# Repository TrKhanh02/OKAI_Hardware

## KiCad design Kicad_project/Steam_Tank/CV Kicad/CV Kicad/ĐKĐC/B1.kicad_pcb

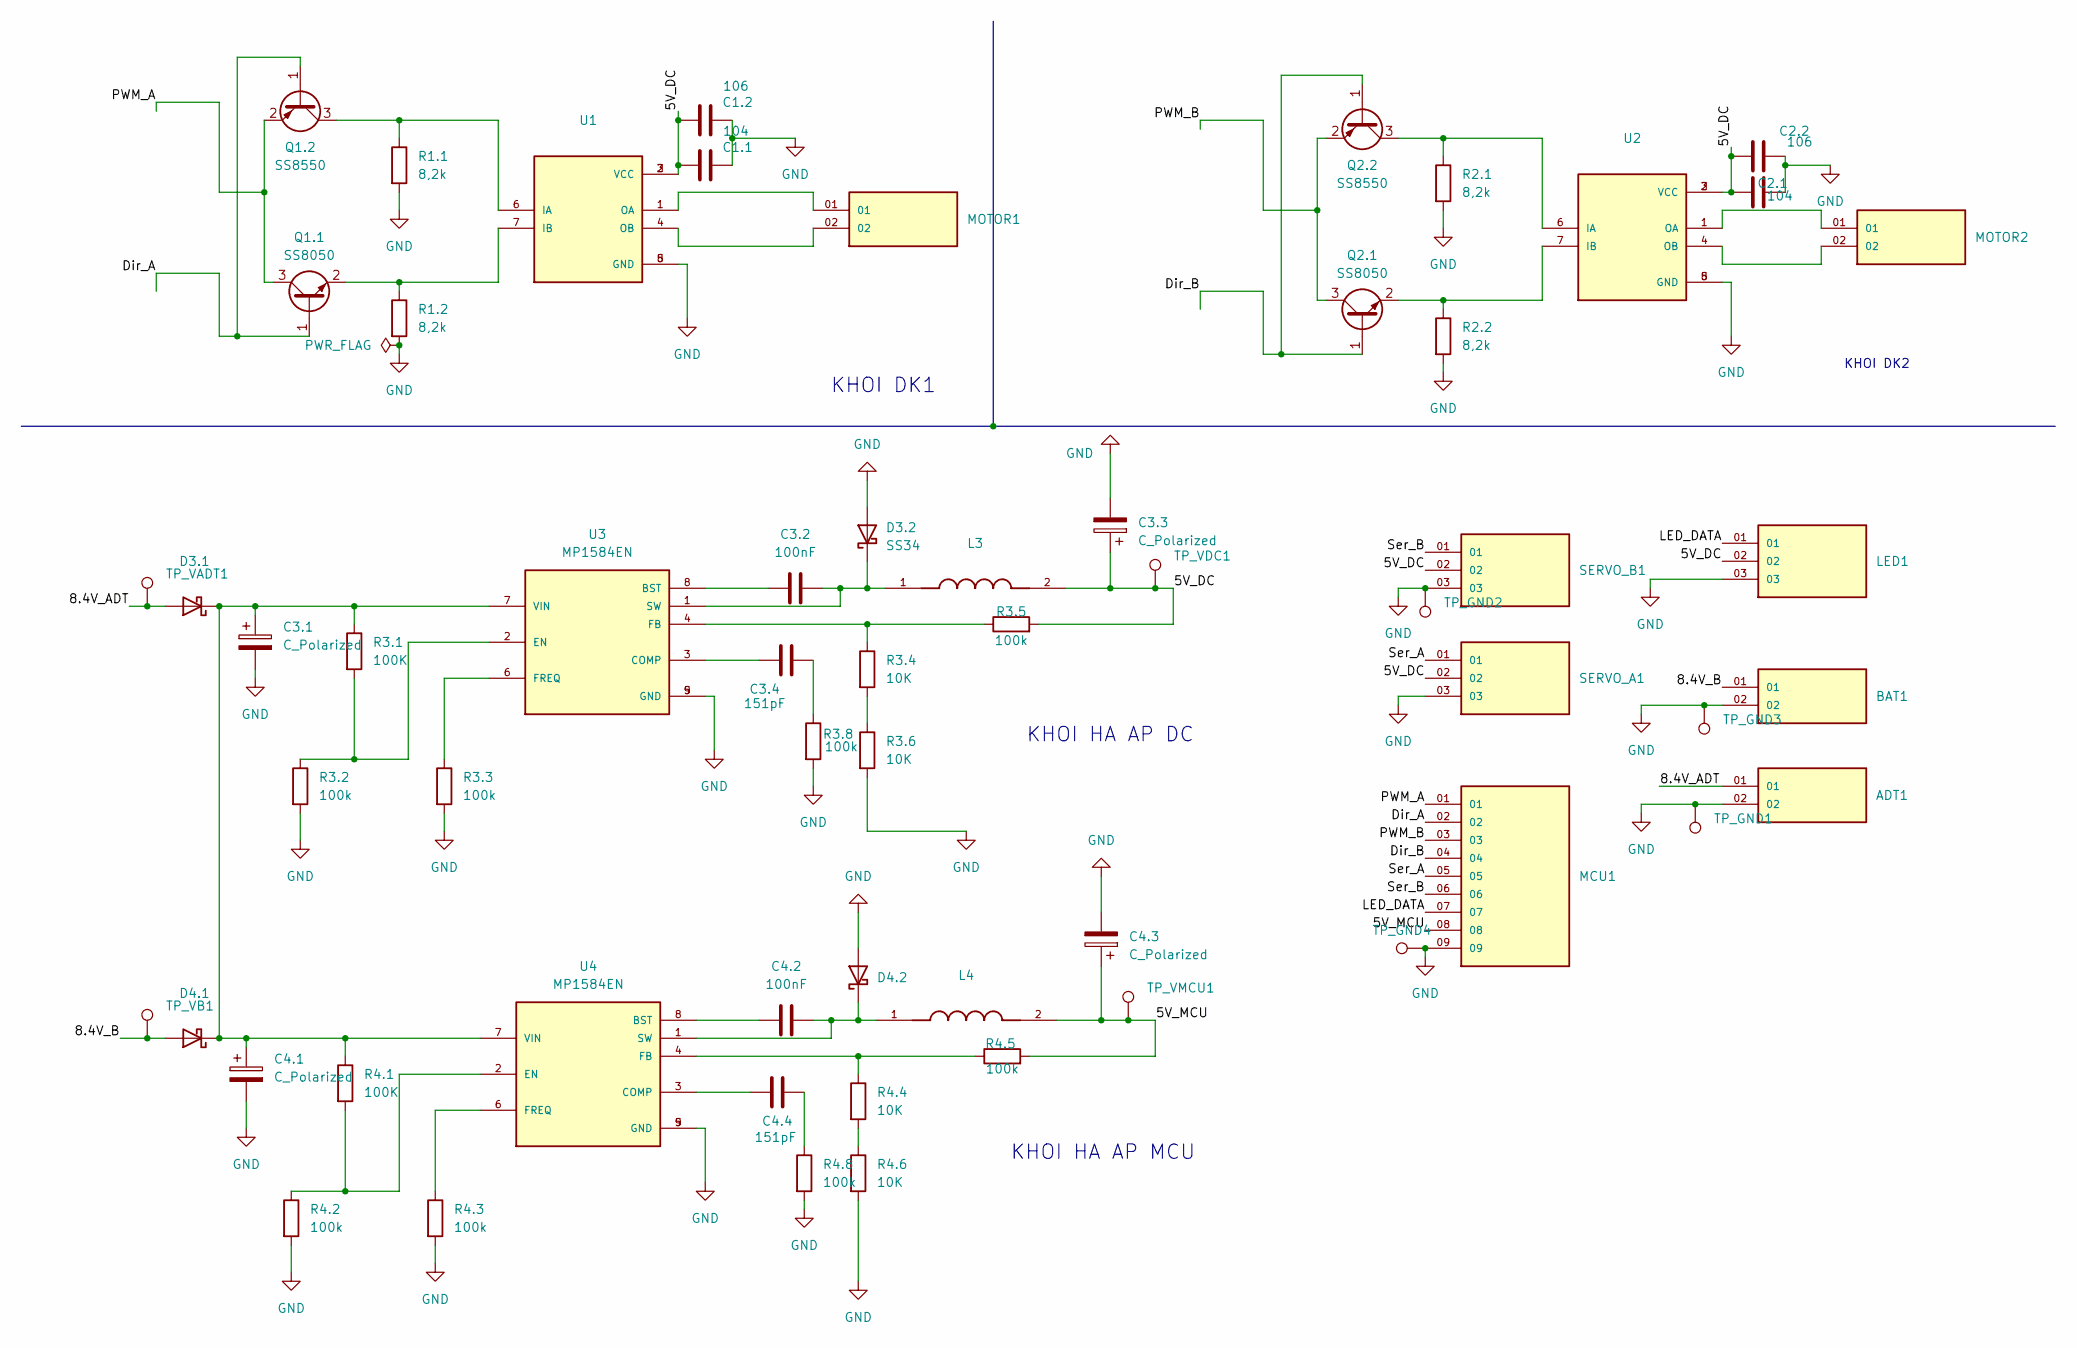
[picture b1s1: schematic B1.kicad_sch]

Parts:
ADT1: TSW-102-23-T-S; SAMTEC_TSW-102-23-T-S; PARTREV R
BAT1: TSW-102-23-T-S; SAMTEC_TSW-102-23-T-S; PARTREV R
C1.1, C2.1: 104; C_0805_2012Metric_Pad1.18x1.45mm_HandSolder
C1.2, C2.2: 106; C_0805_2012Metric_Pad1.18x1.45mm_HandSolder
C3.1, C3.3, C4.1, C4.3: C_Polarized; CP_Elec_6.3x7.7
C3.2, C4.2: 100nF; C_0805_2012Metric_Pad1.18x1.45mm_HandSolder
C3.4, C4.4: 151pF; C_0805_2012Metric_Pad1.18x1.45mm_HandSolder
D3.1, D3.2, D4.1, D4.2: SS34; D_SMA
L3, L4: SLF7032T-331MR22-2PF; IND_SLF7032T-331MR22-2PF; PARTREV N/A
LED1: MTSW-103-10-S-S-580; SAMTEC_MTSW-103-10-S-S-580; PARTREV R
MCU1: MTSW-109-12-L-S-805; SAMTEC_MTSW-109-12-L-S-805; PARTREV R
MOTOR1, MOTOR2: TSW-102-23-T-S; SAMTEC_TSW-102-23-T-S; PARTREV R
Q1.1, Q2.1: SS8050; SOT-23
Q1.2, Q2.2: SS8550; SOT-23
R1.1, R1.2, R2.1, R2.2: 8,2k; R_0805_2012Metric_Pad1.20x1.40mm_HandSolder
R3.1, R4.1: 100K; R_0805_2012Metric_Pad1.20x1.40mm_HandSolder
R3.2, R3.3, R3.5, R3.8, R4.2, R4.3, R4.5, R4.8: 100k; R_0805_2012Metric_Pad1.20x1.40mm_HandSolder
R3.4, R3.6, R4.4, R4.6: 10K; R_0805_2012Metric_Pad1.20x1.40mm_HandSolder
SERVO_A1: MTSW-103-10-S-S-580; SAMTEC_MTSW-103-10-S-S-580; PARTREV R
SERVO_B1: MTSW-103-10-S-S-580; SAMTEC_MTSW-103-10-S-S-580; PARTREV R
TP_GND1, TP_GND2, TP_GND3, TP_GND4: TestPoint; TestPoint_Pad_D1.0mm
TP_VADT1: TestPoint; TestPoint_Pad_D1.0mm
TP_VB1: TestPoint; TestPoint_Pad_D1.0mm
TP_VDC1: TestPoint; TestPoint_Pad_D1.0mm
TP_VMCU1: TestPoint; TestPoint_Pad_D1.0mm
U1, U2: L9110S; SOIC127P599X172-8N; PARTREV NA
U3, U4: MP1584EN; SOIC127P600X170-9N

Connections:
/5V_DC: C1.1.2, C1.2.2, C2.1.2, C2.2.1, C3.3.1, L3.2, LED1.02, R3.5.2, SERVO_A1.02, SERVO_B1.02, TP_VDC1.1, U1.2 (VCC), U1.3 (VCC), U2.2 (VCC), U2.3 (VCC)
/5V_MCU: C4.3.1, L4.2, MCU1.08, R4.5.2, TP_VMCU1.1
/8.4V_ADT: ADT1.01, D3.1.2 (A), TP_VADT1.1
/8.4V_B: BAT1.01, D4.1.2 (A), TP_VB1.1
/Dir_A: MCU1.02, Q1.1.1 (B), Q1.2.1 (B)
/Dir_B: MCU1.04, Q2.1.1 (B), Q2.2.1 (B)
/LED_DATA: LED1.01, MCU1.07
/PWM_A: MCU1.01, Q1.1.3 (C), Q1.2.2 (E)
/PWM_B: MCU1.03, Q2.1.3 (C), Q2.2.2 (E)
/Ser_A: MCU1.05, SERVO_A1.01
/Ser_B: MCU1.06, SERVO_B1.01
GND: ADT1.02, BAT1.02, C1.1.1, C1.2.1, C2.1.1, C2.2.2, C3.1.2, C3.3.2, C4.1.2, C4.3.2, D3.2.2 (A), D4.2.2 (A), LED1.03, MCU1.09, R1.1.2, R1.2.2, R2.1.2, R2.2.2, R3.2.2, R3.3.2, R3.6.2, R3.8.2, R4.2.2, R4.3.2, R4.6.2, R4.8.2, SERVO_A1.03, SERVO_B1.03, TP_GND1.1, TP_GND2.1, TP_GND3.1, TP_GND4.1, U1.5 (GND), U1.8 (GND), U2.5 (GND), U2.8 (GND), U3.5 (GND), U3.9 (GND), U4.5 (GND), U4.9 (GND)
unnamed: C3.4.1, R3.8.1
unnamed: C4.4.2, R4.8.1
unnamed: C3.1.1, C4.1.1, D3.1.1 (K), D4.1.1 (K), R3.1.1, R4.1.1, U3.7 (VIN), U4.7 (VIN)
unnamed: C3.2.2, D3.2.1 (K), L3.1, U3.1 (SW)
unnamed: C4.2.2, D4.2.1 (K), L4.1, U4.1 (SW)
unnamed: Q1.1.2 (E), R1.2.1, U1.7 (IB)
unnamed: Q1.2.3 (C), R1.1.1, U1.6 (IA)
unnamed: Q2.1.2 (E), R2.2.1, U2.7 (IB)
unnamed: Q2.2.3 (C), R2.1.1, U2.6 (IA)
unnamed: R3.4.2, R3.6.1
unnamed: R4.4.2, R4.6.1
unnamed: MOTOR1.01, U1.1 (OA)
unnamed: MOTOR1.02, U1.4 (OB)
unnamed: MOTOR2.01, U2.1 (OA)
unnamed: MOTOR2.02, U2.4 (OB)
unnamed: C3.2.1, U3.8 (BST)
unnamed: C3.4.2, U3.3 (COMP)
unnamed: R3.1.2, R3.2.1, U3.2 (EN)
unnamed: R3.4.1, R3.5.1, U3.4 (FB)
unnamed: R3.3.1, U3.6 (FREQ)
unnamed: C4.2.1, U4.8 (BST)
unnamed: C4.4.1, U4.3 (COMP)
unnamed: R4.1.2, R4.2.1, U4.2 (EN)
unnamed: R4.4.1, R4.5.1, U4.4 (FB)
unnamed: R4.3.1, U4.6 (FREQ)

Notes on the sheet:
KHOI HA AP DC
KHOI DK1
KHOI DK2
KHOI HA AP MCU

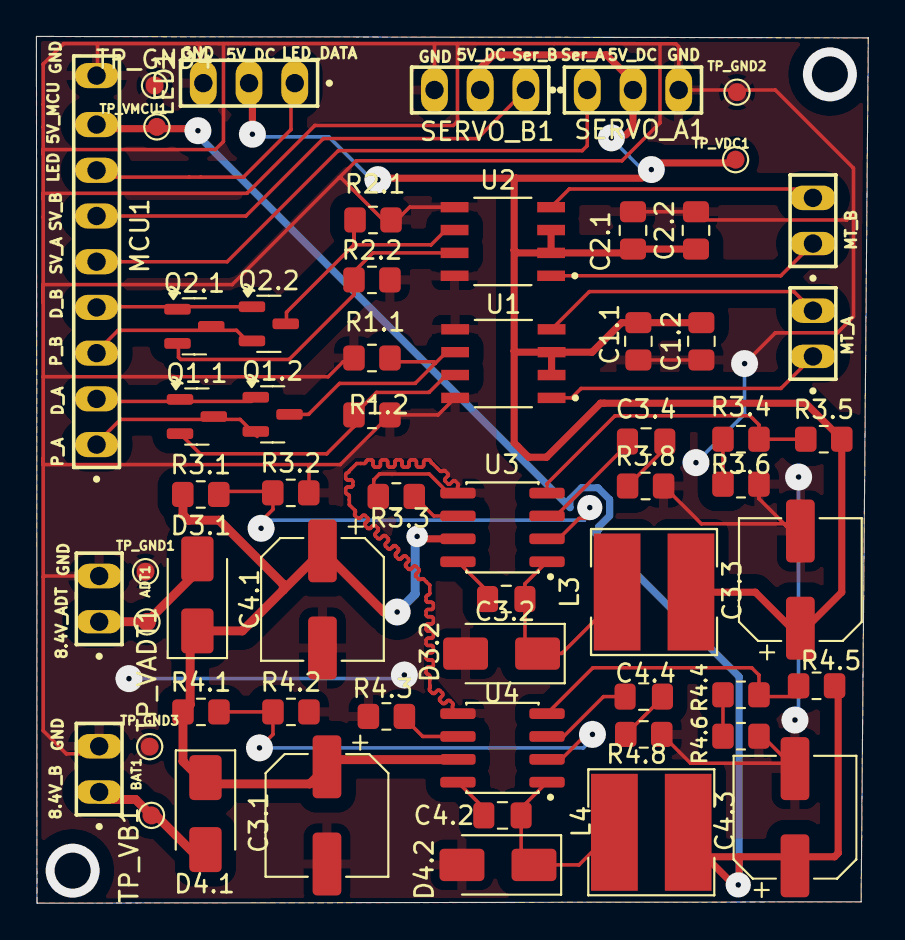
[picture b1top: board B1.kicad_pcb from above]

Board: 2 copper layers, 46.2 x 48.1 mm, 60 parts (0 on the bottom side), 37 nets.

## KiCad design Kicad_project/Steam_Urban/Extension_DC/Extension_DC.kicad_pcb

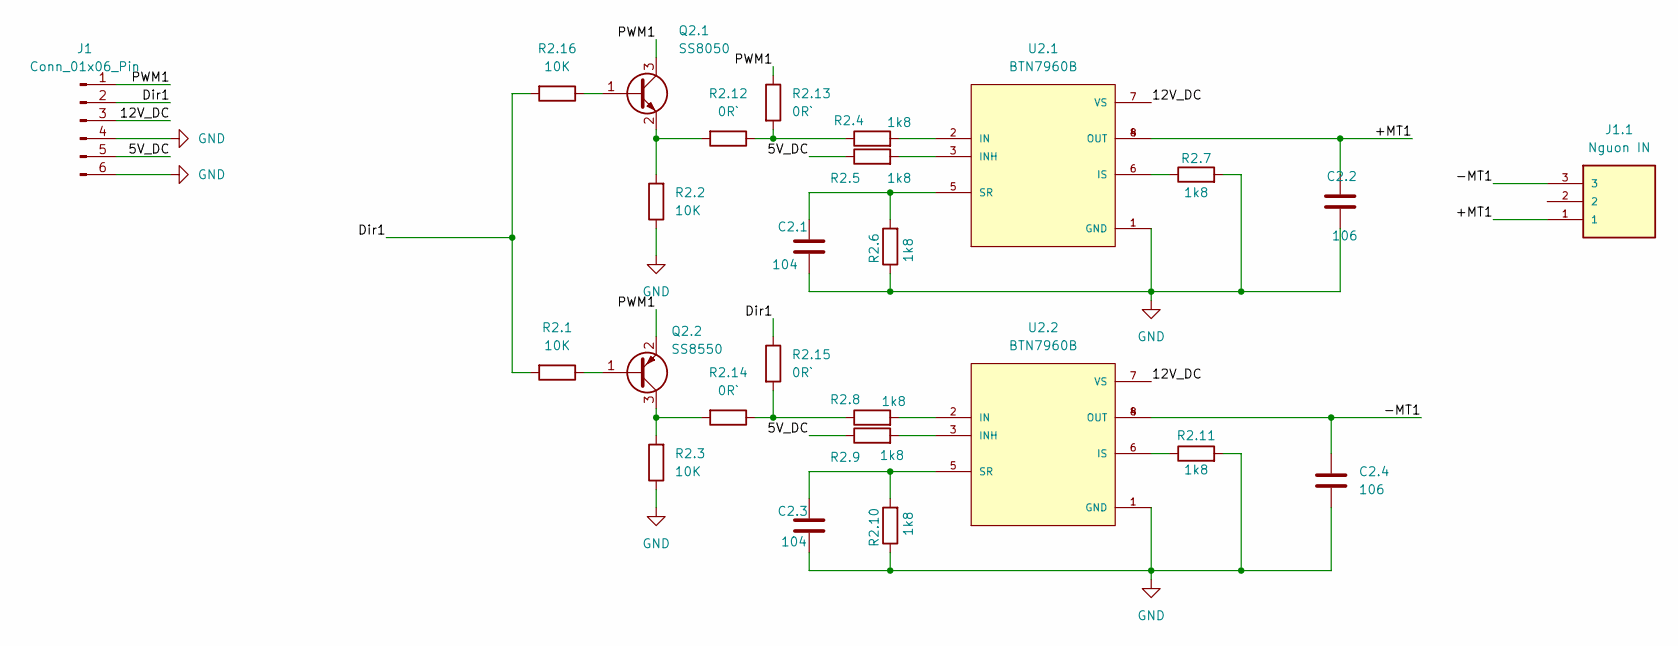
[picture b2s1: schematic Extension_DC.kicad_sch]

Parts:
C2.1, C2.3: 104; C_0805_2012Metric
C2.2, C2.4: 106; C_0805_2012Metric
J1: Conn_01x06_Pin; PinHeader_1x06_P2.54mm_Vertical
J1.1: Nguon IN; CUI_TBP04R1-500-03BE; PARTREV 1.0
Q2.1: SS8050; SOT-23
Q2.2: SS8550; SOT-23
R2.1, R2.2, R2.3, R2.16: 10K; R_0805_2012Metric_Pad1.20x1.40mm_HandSolder
R2.4, R2.5, R2.6, R2.7, R2.8, R2.9, R2.10, R2.11: 1k8; R_0805_2012Metric
R2.12, R2.13, R2.14, R2.15: 0R`; R_0805_2012Metric_Pad1.20x1.40mm_HandSolder
U2.1, U2.2: BTN7960B; DPAK127P1490X440-8N; PARTREV 1.1

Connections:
/5V_DC: J1.5, R2.5.1, R2.9.1
/12V_DC: J1.3, U2.1.7 (VS), U2.2.7 (VS)
/+MT1: C2.2.2, J1.1.1, U2.1.4 (OUT), U2.1.8 (OUT)
/-MT1: C2.4.2, J1.1.3, U2.2.4 (OUT), U2.2.8 (OUT)
/Dir1: J1.2, R2.1.2, R2.15.1, R2.16.2
/PWM1: J1.1, Q2.1.3 (C), Q2.2.2 (E), R2.13.1
GND: C2.1.1, C2.2.1, C2.3.1, C2.4.1, J1.4, J1.6, R2.2.1, R2.3.1, R2.6.1, R2.7.2, R2.10.1, R2.11.2, U2.1.1 (GND), U2.2.1 (GND)
unnamed: Q2.1.1 (B), R2.16.1
unnamed: Q2.1.2 (E), R2.2.2, R2.12.2
unnamed: Q2.2.1 (B), R2.1.1
unnamed: Q2.2.3 (C), R2.3.2, R2.14.2
unnamed: R2.4.1, R2.12.1, R2.13.2
unnamed: R2.8.1, R2.14.1, R2.15.2
unnamed: R2.4.2, U2.1.2 (IN)
unnamed: R2.5.2, U2.1.3 (INH)
unnamed: R2.7.1, U2.1.6 (IS)
unnamed: C2.1.2, R2.6.2, U2.1.5 (SR)
unnamed: R2.8.2, U2.2.2 (IN)
unnamed: R2.9.2, U2.2.3 (INH)
unnamed: R2.11.1, U2.2.6 (IS)
unnamed: C2.3.2, R2.10.2, U2.2.5 (SR)

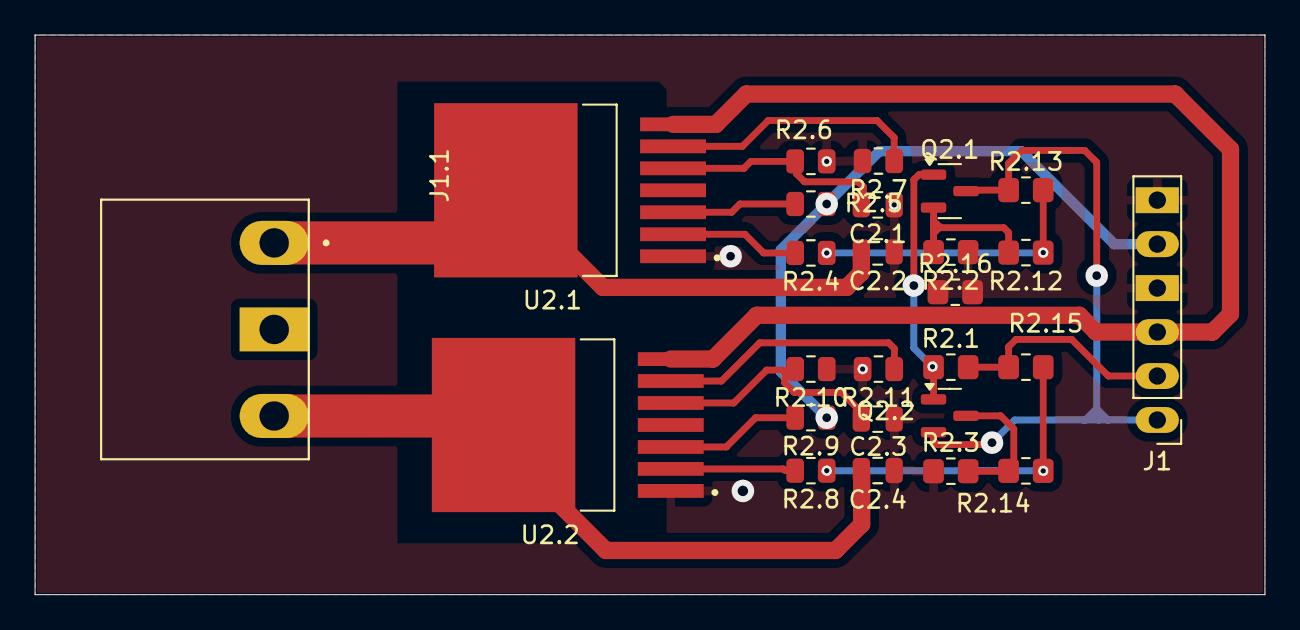
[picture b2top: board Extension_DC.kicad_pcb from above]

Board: 2 copper layers, 71.1 x 32.3 mm, 26 parts (0 on the bottom side), 21 nets.

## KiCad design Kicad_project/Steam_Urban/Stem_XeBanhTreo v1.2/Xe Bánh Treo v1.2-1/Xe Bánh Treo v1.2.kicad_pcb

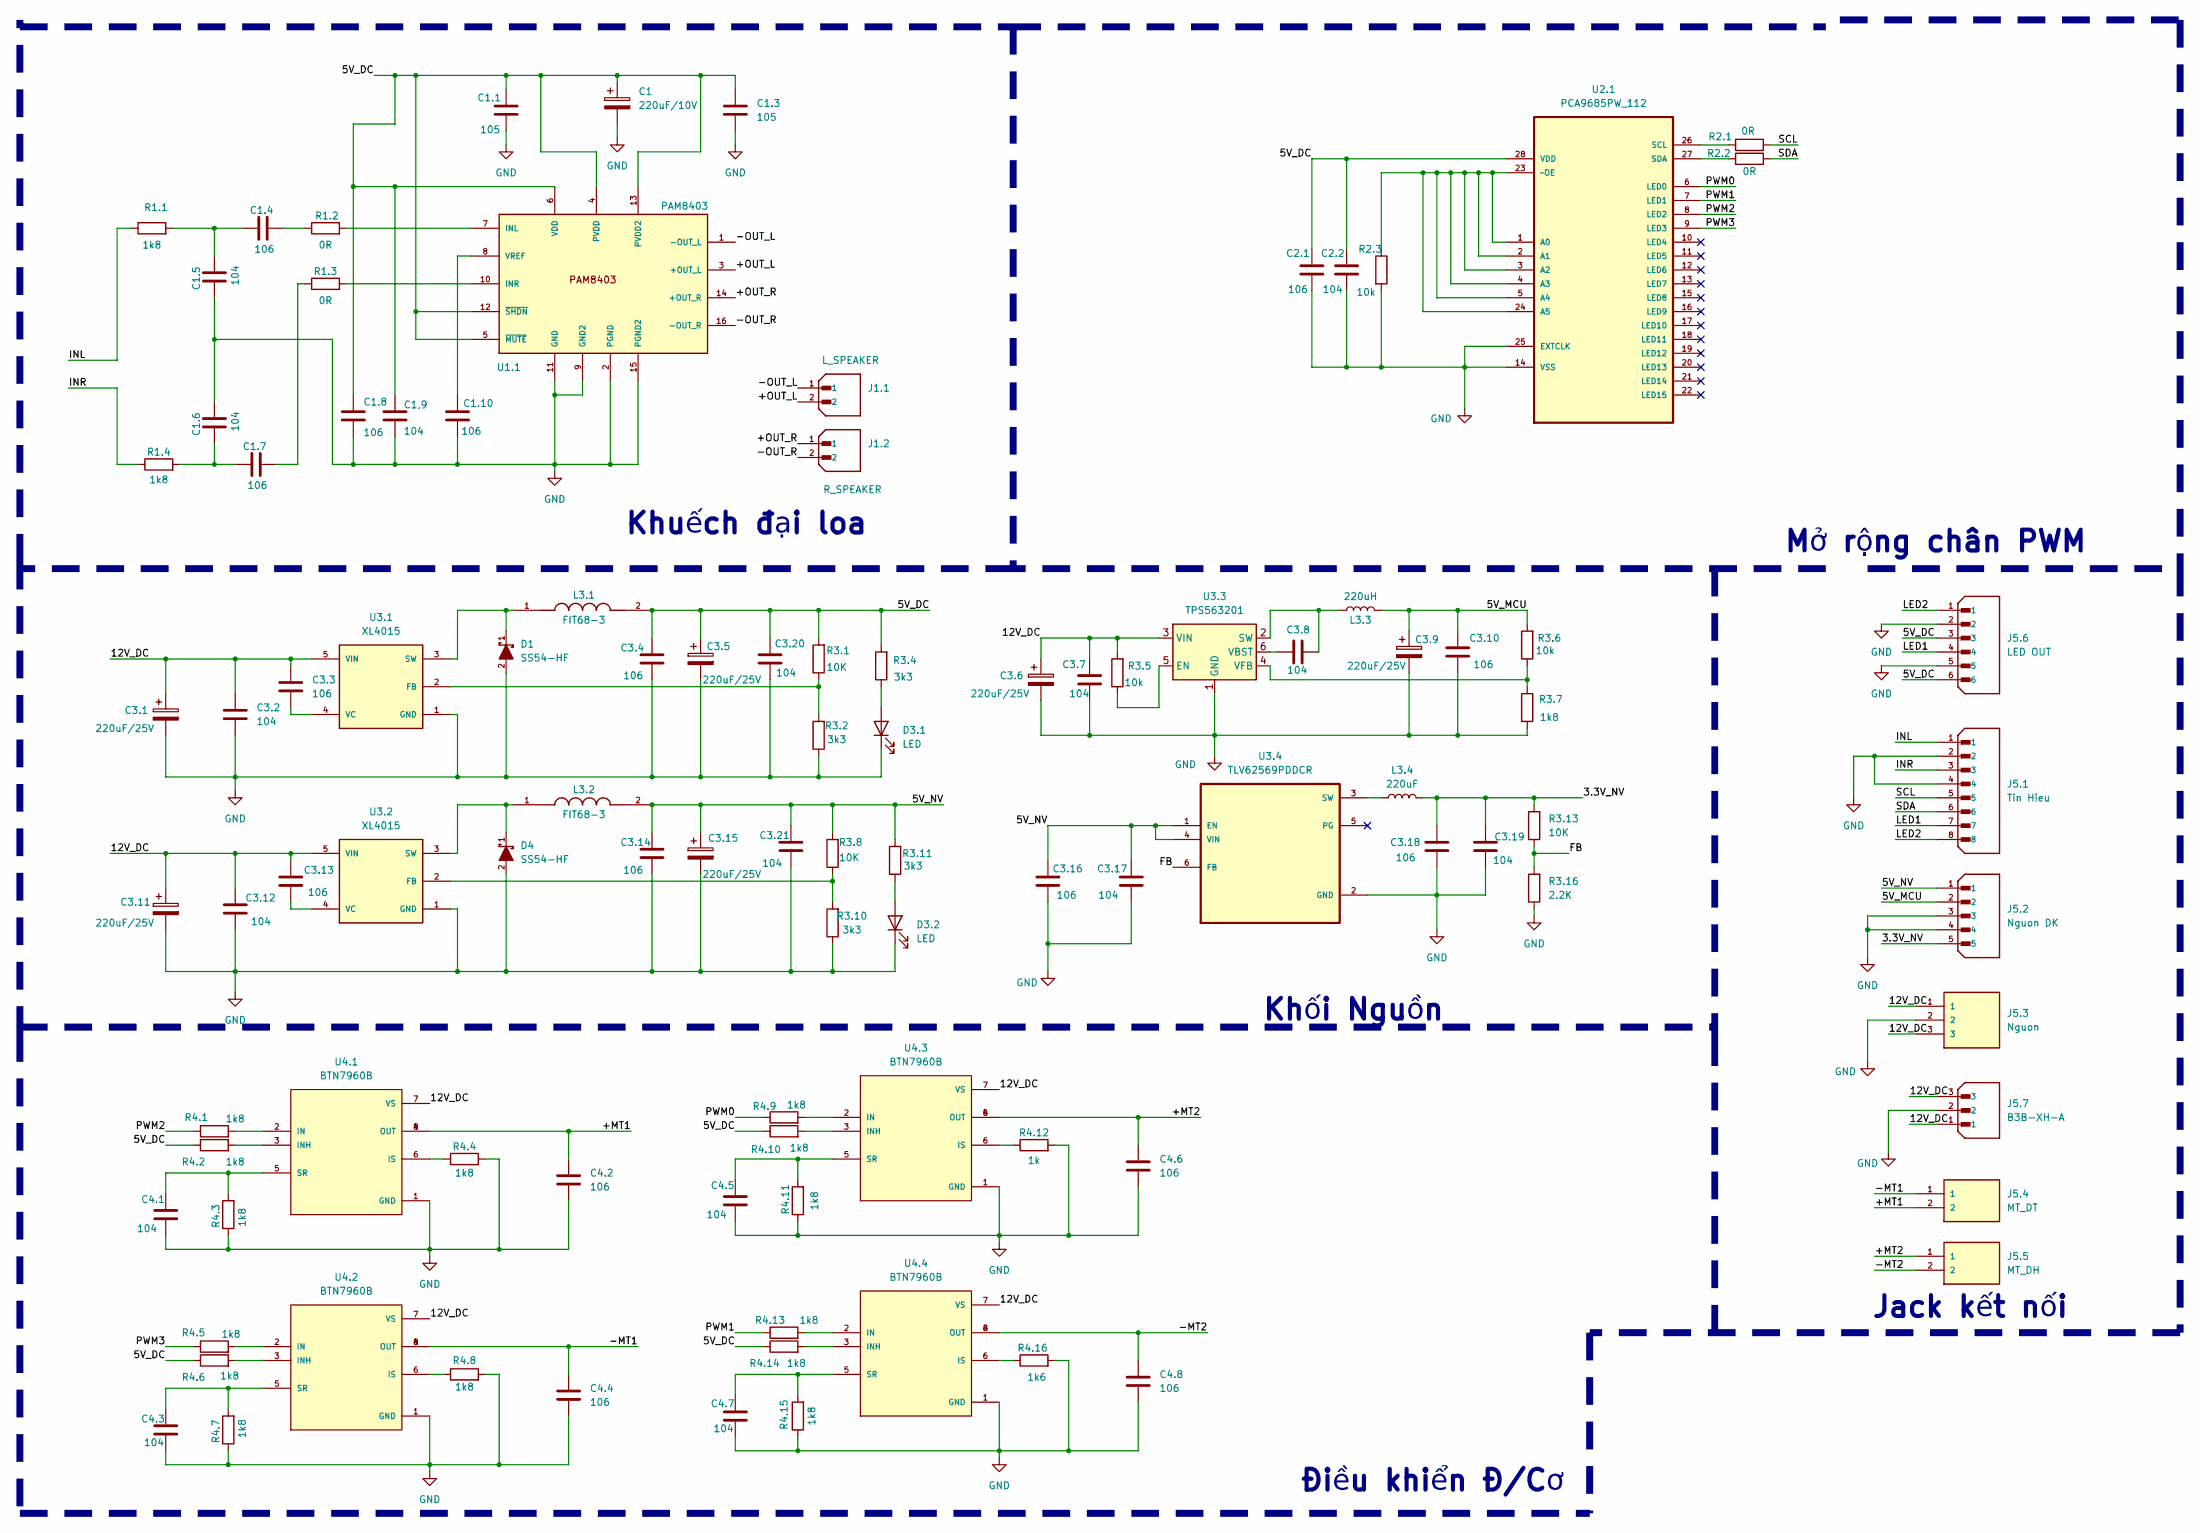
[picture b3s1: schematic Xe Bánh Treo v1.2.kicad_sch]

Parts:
C1: 220uF/10V; CP_Elec_6.3x5.4
C1,9, C1.5, C1.6, C2.2, C3.2, C3.7, C3.8, C3.12, C3.17, C3.19, C3.20, C3.21, C4.1, C4.3, C4.5, C4.7: 104; C_0805_2012Metric
C1.1, C1.3: 105; C_0805_2012Metric
C1.4, C1.7, C1.8, C1.10, C2.1, C3.3, C3.4, C3.10, C3.13, C3.14, C3.16, C3.18, C4.2, C4.4, C4.6, C4.8: 106; C_0805_2012Metric
C3.1, C3.5, C3.6, C3.9, C3.11, C3.15: 220uF/25V; CP_Elec_8x10.5
D1, D4: SS54-HF; DIOM5025X220N; MOUSER_PART_NUMBER 750-SS54-HF
D3.1, D3.2: LED; LED_0805_2012Metric
J1.1: L_SPEAKER; JST_B2B-XH-A; PARTREV N/A
J1.2: R_SPEAKER; JST_B2B-XH-A; PARTREV N/A
J5.1: Tin Hieu; JST_B8B-XH-A; PARTREV 7/4/21
J5.2: Nguon DK; JST_B5B-XH-A; PARTREV 7/4/21
J5.3: Nguon; CUI_TBP04R1-500-03BE; PARTREV 1.0
J5.4: MT_DT; CUI_TBP04R1-500-02BE; PARTREV 1.0
J5.5: MT_DH; CUI_TBP04R1-500-02BE; PARTREV 1.0
J5.6: LED OUT; JST_B6B-XH-A; PARTREV 7/4/21
J5.7: B3B-XH-A; JST_B3B-XH-A; PARTREV 7/4/21
L3.1, L3.2: FIT68-3; IND_FIT68-3; PARTREV N/A
L3.3: 220uH; L_7.3x7.3_H4.5
L3.4: 220uF; L_7.3x7.3_H4.5
R1.1, R1.4, R3.7, R4.1, R4.2, R4.3, R4.4, R4.5, R4.6, R4.7, R4.8, R4.9, R4.10, R4.11, R4.13, R4.14, R4.15: 1k8; R_0805_2012Metric
R1.2, R1.3, R2.1, R2.2: 0R; R_0805_2012Metric
R2.3, R3.5, R3.6: 10k; R_0805_2012Metric
R3.1, R3.8, R3.13: 10K; R_0805_2012Metric
R3.2, R3.4, R3.10, R3.11: 3k3; R_0805_2012Metric
R3.16: 2.2K; R_0805_2012Metric
R4.12: 1k; R_0805_2012Metric
R4.16: 1k6; R_0805_2012Metric
U1.1: PAM8403; SOP-16
U2.1: PCA9685PW_112; SOP65P640X110-28N; MPN PCA9685PW,112
U3.1, U3.2: XL4015; CONV_XL4015; PARTREV 1.5
U3.3: TPS563201; SOT-23-6
U3.4: TLV62569PDDCR; SOT95P280X110-6N
U4.1, U4.2, U4.3, U4.4: BTN7960B; DPAK127P1490X440-8N; PARTREV 1.1

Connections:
/3.3V_NV: C3.18.1, C3.19.1, J5.2.5, L3.4.1, R3.13.2
/5V_DC: C1.1, C1,9.2, C1.1.2, C1.3.2, C1.8.2, C2.1.1, C2.2.1, C3.4.1, C3.5.1, C3.20.1, J5.6.3, J5.6.6, L3.1.2, R3.1.2, R3.4.2, R4.2.1, R4.6.1, R4.10.1, R4.14.1, U1.1.4 (PVDD), U1.1.5 (~MUTE), U1.1.6 (VDD), U1.1.12 (~SHDN), U1.1.13 (PVDD2), U2.1.28 (VDD)
/5V_MCU: C3.9.1, C3.10.1, J5.2.2, L3.3.2, R3.6.2
/5V_NV: C3.14.1, C3.15.1, C3.16.1, C3.17.1, C3.21.1, J5.2.1, L3.2.2, R3.8.2, R3.11.2, U3.4.1 (EN), U3.4.4 (VIN)
/12V_DC: C3.1.1, C3.2.1, C3.3.1, C3.6.1, C3.7.1, C3.11.1, C3.12.1, C3.13.1, J5.3.1, J5.3.3, J5.7.1, J5.7.3, R3.5.2, U3.1.5 (VIN), U3.2.5 (VIN), U3.3.3 (VIN), U4.1.7 (VS), U4.2.7 (VS), U4.3.7 (VS), U4.4.7 (VS)
/+MT1: C4.2.2, J5.4.2, U4.1.4 (OUT), U4.1.8 (OUT)
/+MT2: C4.6.2, J5.5.1, U4.3.4 (OUT), U4.3.8 (OUT)
/+OUT_L: J1.1.2, U1.1.3 (+OUT_L)
/+OUT_R: J1.2.1, U1.1.14 (+OUT_R)
/-MT1: C4.4.2, J5.4.1, U4.2.4 (OUT), U4.2.8 (OUT)
/-MT2: C4.8.2, J5.5.2, U4.4.4 (OUT), U4.4.8 (OUT)
/-OUT_L: J1.1.1, U1.1.1 (-OUT_L)
/-OUT_R: J1.2.2, U1.1.16 (-OUT_R)
/FB: R3.13.1, R3.16.2, U3.4.6 (FB)
/INL: J5.1.1, R1.1.1
/INR: J5.1.3, R1.4.1
/LED1: J5.1.7, J5.6.4
/LED2: J5.1.8, J5.6.1
/PWM0: R4.9.1, U2.1.6 (LED0)
/PWM1: R4.13.1, U2.1.7 (LED1)
/PWM2: R4.1.1, U2.1.8 (LED2)
/PWM3: R4.5.1, U2.1.9 (LED3)
/SCL: J5.1.5, R2.1.2
/SDA: J5.1.6, R2.2.2
GND: C1.2, C1,9.1, C1.1.1, C1.3.1, C1.5.2, C1.6.1, C1.8.1, C1.10.1, C2.1.2, C2.2.2, C3.1.2, C3.2.2, C3.4.2, C3.5.2, C3.6.2, C3.7.2, C3.9.2, C3.10.2, C3.11.2, C3.12.2, C3.14.2, C3.15.2, C3.16.2, C3.17.2, C3.18.2, C3.19.2, C3.20.2, C3.21.2, C4.1.1, C4.2.1, C4.3.1, C4.4.1, C4.5.1, C4.6.1, C4.7.1, C4.8.1, D1.2, D3.1.1 (K), D3.2.1 (K), D4.2, J5.1.2, J5.1.4, J5.2.3, J5.2.4, J5.3.2, J5.6.2, J5.6.5, J5.7.2, R2.3.2, R3.2.1, R3.7.2, R3.10.1, R3.16.1, R4.3.1, R4.4.2, R4.7.1, R4.8.2, R4.11.1, R4.12.2, R4.15.1, R4.16.2, U1.1.2 (PGND), U1.1.9 (GND2), U1.1.11 (GND), U1.1.15 (PGND2), U2.1.14 (VSS), U2.1.25 (EXTCLK), U3.1.1 (GND), U3.2.1 (GND), U3.3.1 (GND), U3.4.2 (GND), U4.1.1 (GND), U4.2.1 (GND), U4.3.1 (GND), U4.4.1 (GND)
unnamed: C1.4.1, R1.2.1
unnamed: C1.4.2, C1.5.1, R1.1.2
unnamed: C1.6.2, C1.7.2, R1.4.2
unnamed: C1.7.1, R1.3.1
unnamed: D3.1.2 (A), R3.4.1
unnamed: D3.2.2 (A), R3.11.1
unnamed: R1.2.2, U1.1.7 (INL)
unnamed: R1.3.2, U1.1.10 (INR)
unnamed: C1.10.2, U1.1.8 (VREF)
unnamed: R2.3.1, U2.1.1 (A0), U2.1.2 (A1), U2.1.3 (A2), U2.1.4 (A3), U2.1.5 (A4), U2.1.23 (~OE), U2.1.24 (A5)
unnamed: R2.1.1, U2.1.26 (SCL)
unnamed: R2.2.1, U2.1.27 (SDA)
unnamed: R3.1.1, R3.2.2, U3.1.2 (FB)
unnamed: D1.1, L3.1.1, U3.1.3 (SW)
unnamed: C3.3.2, U3.1.4 (VC)
unnamed: R3.8.1, R3.10.2, U3.2.2 (FB)
unnamed: D4.1, L3.2.1, U3.2.3 (SW)
unnamed: C3.13.2, U3.2.4 (VC)
unnamed: R3.5.1, U3.3.5 (EN)
unnamed: C3.8.2, L3.3.1, U3.3.2 (SW)
unnamed: C3.8.1, U3.3.6 (VBST)
unnamed: R3.6.1, R3.7.1, U3.3.4 (VFB)
unnamed: L3.4.2, U3.4.3 (SW)
unnamed: R4.1.2, U4.1.2 (IN)
unnamed: R4.2.2, U4.1.3 (INH)
unnamed: R4.4.1, U4.1.6 (IS)
unnamed: C4.1.2, R4.3.2, U4.1.5 (SR)
unnamed: R4.5.2, U4.2.2 (IN)
unnamed: R4.6.2, U4.2.3 (INH)
unnamed: R4.8.1, U4.2.6 (IS)
unnamed: C4.3.2, R4.7.2, U4.2.5 (SR)
unnamed: R4.9.2, U4.3.2 (IN)
unnamed: R4.10.2, U4.3.3 (INH)
unnamed: R4.12.1, U4.3.6 (IS)
unnamed: C4.5.2, R4.11.2, U4.3.5 (SR)
unnamed: R4.13.2, U4.4.2 (IN)
unnamed: R4.14.2, U4.4.3 (INH)
unnamed: R4.16.1, U4.4.6 (IS)
unnamed: C4.7.2, R4.15.2, U4.4.5 (SR)

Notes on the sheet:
Khối Nguồn
Điều khiển Đ/Cơ
Mở rộng chân PWM
Jack kết nối
Khuếch đại loa

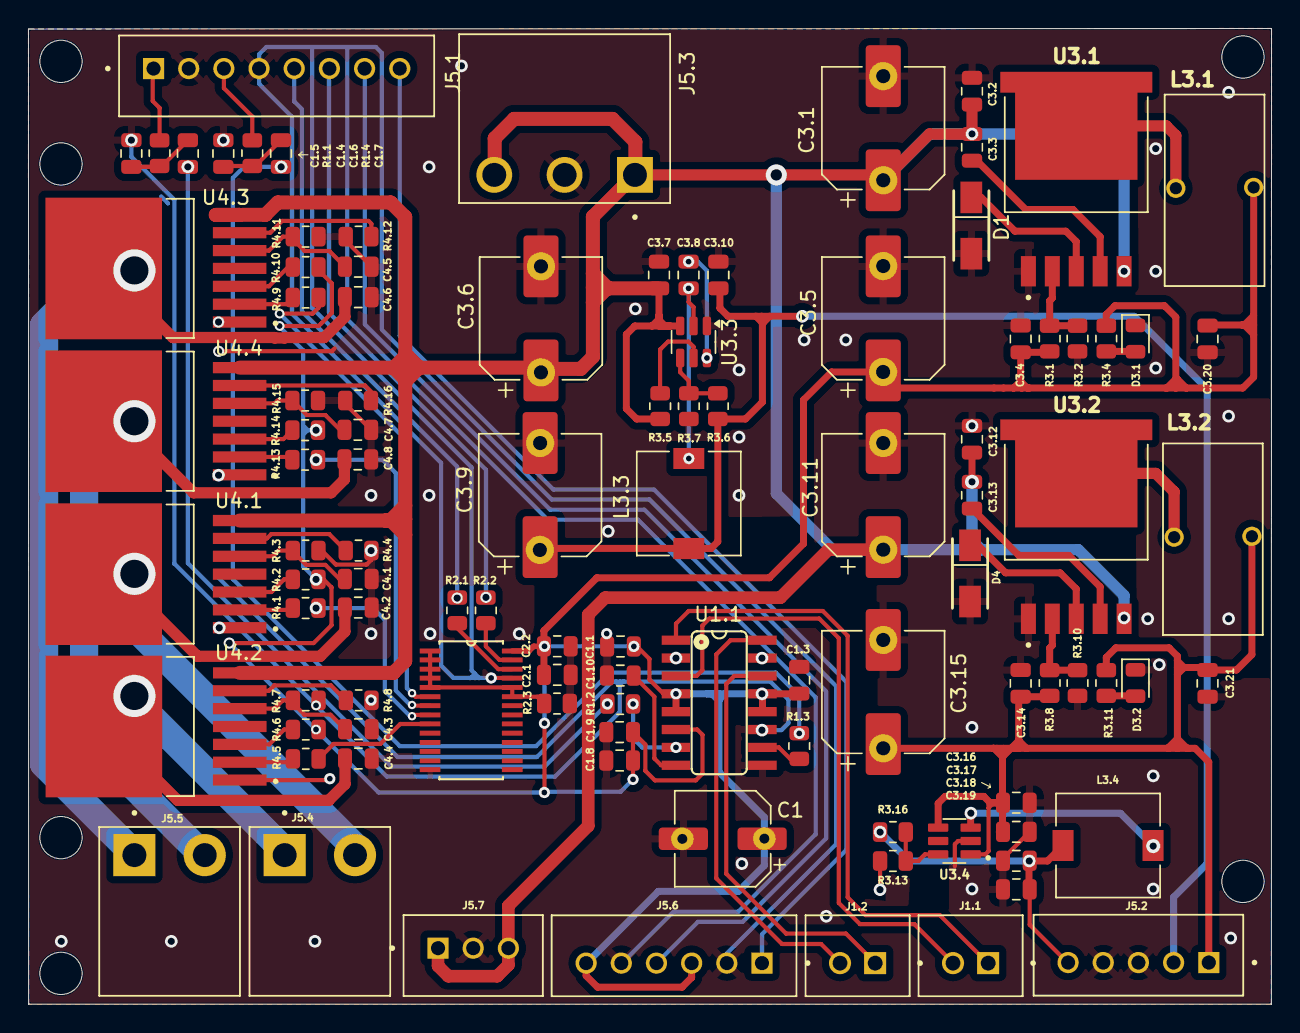
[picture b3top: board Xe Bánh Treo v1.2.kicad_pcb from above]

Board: 2 copper layers, 88.4 x 69.4 mm, 102 parts (0 on the bottom side), 64 nets.

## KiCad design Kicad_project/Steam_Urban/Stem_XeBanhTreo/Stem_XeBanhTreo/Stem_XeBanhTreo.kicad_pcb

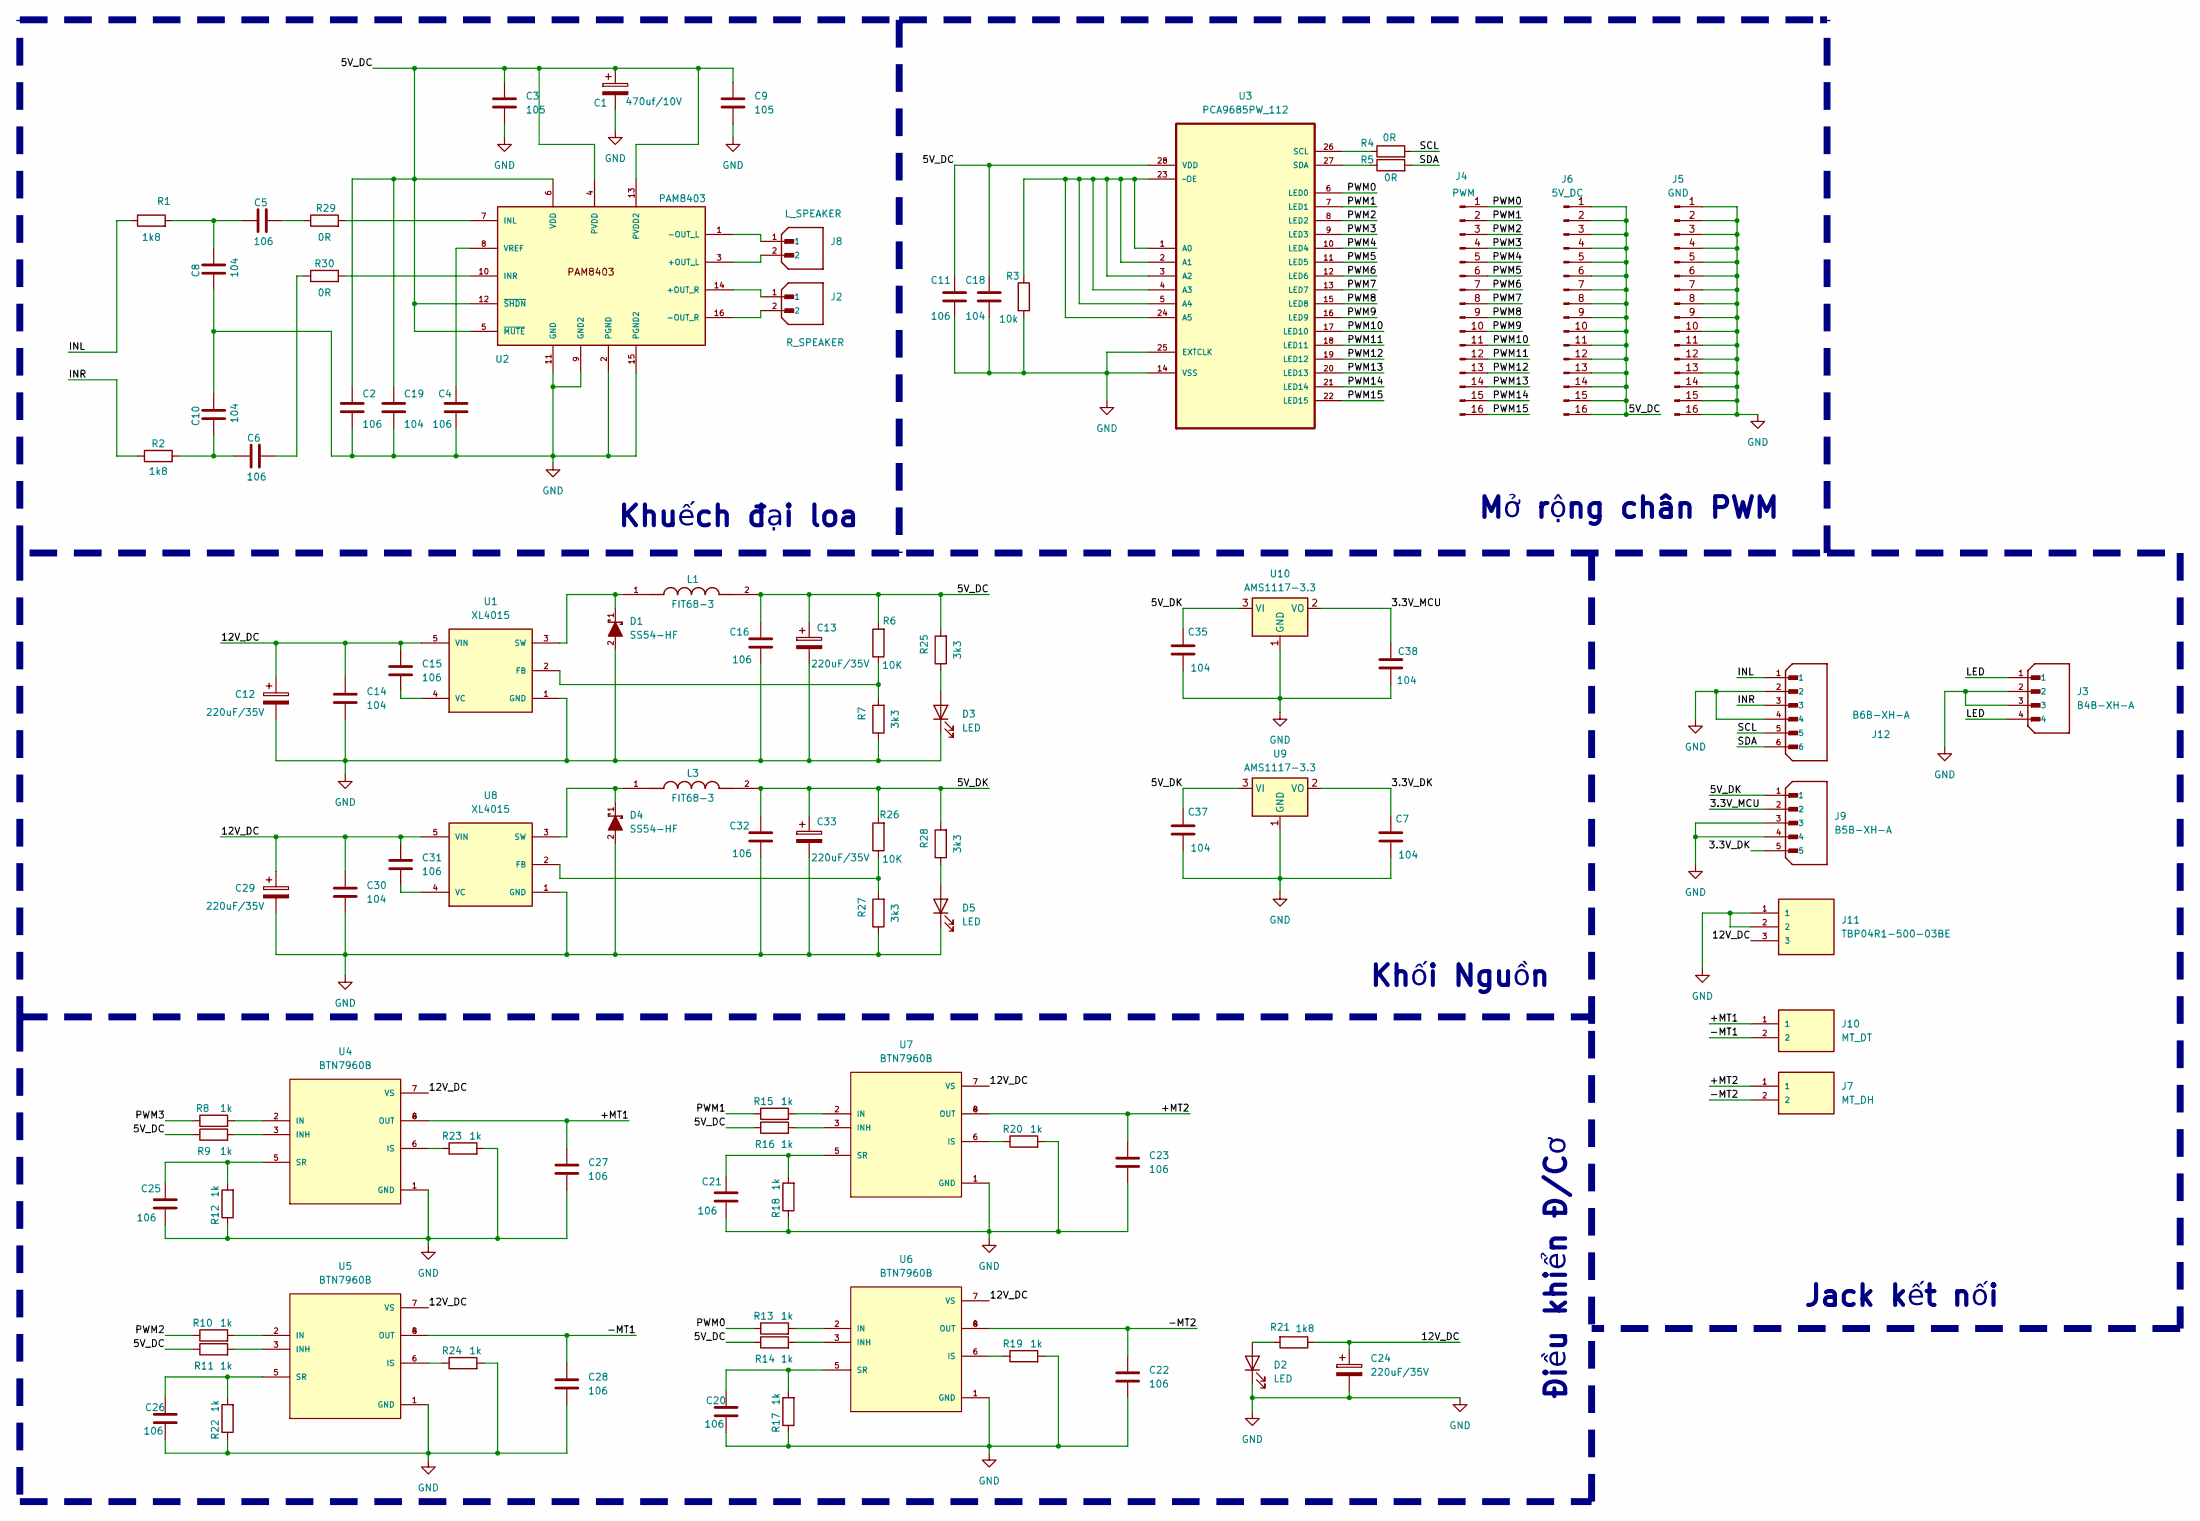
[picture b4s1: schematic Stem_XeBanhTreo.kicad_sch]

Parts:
C1: 470uf/10V; CP_Elec_6.3x7.7
C2, C4, C5, C6, C11, C15, C16, C20, C21, C22, C23, C25, C26, C27, C28, C31, C32: 106; C_0805_2012Metric
C3, C9: 105; C_0805_2012Metric
C7, C8, C10, C14, C18, C19, C30, C35, C37, C38: 104; C_0805_2012Metric
C12, C13, C29, C33: 220uF/35V; CP_Elec_8x10.5
C24: 220uF/35V; CP_Elec_5x5.4
D1, D4: SS54-HF; DIOM5025X220N; MOUSER_PART_NUMBER 750-SS54-HF
D2, D3, D5: LED; LED_0805_2012Metric
J2: R_SPEAKER; JST_B2B-XH-A; PARTREV N/A
J3: B4B-XH-A; JST_B4B-XH-A; PARTREV 7/4/21
J4: PWM; PinHeader_1x16_P2.54mm_Vertical
J5: GND; PinHeader_1x16_P2.54mm_Vertical
J6: 5V_DC; PinHeader_1x16_P2.54mm_Vertical
J7: MT_DH; CUI_TBP04R1-500-02BE; PARTREV 1.0
J8: L_SPEAKER; JST_B2B-XH-A; PARTREV N/A
J9: B5B-XH-A; JST_B5B-XH-A; PARTREV 7/4/21
J10: MT_DT; CUI_TBP04R1-500-02BE; PARTREV 1.0
J11: TBP04R1-500-03BE; CUI_TBP04R1-500-03BE; PARTREV 1.0
J12: B6B-XH-A; JST_B6B-XH-A; PARTREV 7/4/21
L1, L3: FIT68-3; IND_FIT68-3; PARTREV N/A
R1, R2, R21: 1k8; R_0805_2012Metric
R3: 10k; R_0805_2012Metric
R4, R5, R29, R30: 0R; R_0805_2012Metric
R6, R26: 10K; R_0805_2012Metric
R7, R25, R27, R28: 3k3; R_0805_2012Metric
R8, R9, R10, R11, R12, R13, R14, R15, R16, R17, R18, R19, R20, R22, R23, R24: 1k; R_0805_2012Metric
U1, U8: XL4015; CONV_XL4015; PARTREV 1.5
U2: PAM8403; SOP-16
U3: PCA9685PW_112; SOP65P640X110-28N; MPN PCA9685PW,112
U4, U5, U6, U7: BTN7960B; DPAK127P1490X440-8N; PARTREV 1.1
U9, U10: AMS1117-3.3; SOT-223-3_TabPin2

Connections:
/5V_DC: C1.1, C2.2, C3.2, C9.2, C11.1, C13.1, C16.1, C18.1, C19.2, J6.1, J6.2, J6.3, J6.4, J6.5, J6.6, J6.7, J6.8, J6.9, J6.10, J6.11, J6.12, J6.13, J6.14, J6.15, J6.16, L1.2, R6.2, R9.1, R11.1, R14.1, R16.1, R25.2, U2.4 (PVDD), U2.5 (~MUTE), U2.6 (VDD), U2.12 (~SHDN), U2.13 (PVDD2), U3.28 (VDD)
/12V_DC: C12.1, C14.1, C15.1, C24.1, C29.1, C30.1, C31.1, J11.3, R21.1, U1.5 (VIN), U4.7 (VS), U5.7 (VS), U6.7 (VS), U7.7 (VS), U8.5 (VIN)
/+MT1: C27.2, J10.1, U4.4 (OUT), U4.8 (OUT)
/+MT2: C23.2, J7.1, U7.4 (OUT), U7.8 (OUT)
/-MT1: C28.2, J10.2, U5.4 (OUT), U5.8 (OUT)
/-MT2: C22.2, J7.2, U6.4 (OUT), U6.8 (OUT)
/PWM0: J4.1, R13.1, U3.6 (LED0)
/PWM1: J4.2, R15.1, U3.7 (LED1)
/PWM2: J4.3, R10.1, U3.8 (LED2)
/PWM3: J4.4, R8.1, U3.9 (LED3)
/PWM4: J4.5, U3.10 (LED4)
/PWM5: J4.6, U3.11 (LED5)
/PWM6: J4.7, U3.12 (LED6)
/PWM7: J4.8, U3.13 (LED7)
/PWM8: J4.9, U3.15 (LED8)
/PWM9: J4.10, U3.16 (LED9)
/PWM10: J4.11, U3.17 (LED10)
/PWM11: J4.12, U3.18 (LED11)
/PWM12: J4.13, U3.19 (LED12)
/PWM13: J4.14, U3.20 (LED13)
/PWM14: J4.15, U3.21 (LED14)
/PWM15: J4.16, U3.22 (LED15)
/SCL: J12.5, R4.2; also elsewhere on the board
/SDA: J12.6, R5.2; also elsewhere on the board
unnamed: C5.1, R29.1
unnamed: C5.2, C8.1, R1.2
unnamed: C6.1, R30.1
unnamed: C6.2, C10.2, R2.2
unnamed: D2.2 (A), R21.2
unnamed: D3.2 (A), R25.1
unnamed: D5.2 (A), R28.1
unnamed: J3.1, J3.4
unnamed 32: J12.1, R1.1; also elsewhere on the board
unnamed 33: J12.3, R2.1; also elsewhere on the board
unnamed: R6.1, R7.2, U1.2 (FB)
unnamed: D1.1, L1.1, U1.3 (SW)
unnamed: C15.2, U1.4 (VC)
unnamed: J8.2, U2.3 (+OUT_L)
unnamed: J2.1, U2.14 (+OUT_R)
unnamed: J8.1, U2.1 (-OUT_L)
unnamed: J2.2, U2.16 (-OUT_R)
unnamed: R29.2, U2.7 (INL)
unnamed: R30.2, U2.10 (INR)
unnamed: C4.2, U2.8 (VREF)
unnamed: R3.1, U3.1 (A0), U3.2 (A1), U3.3 (A2), U3.4 (A3), U3.5 (A4), U3.23 (~OE), U3.24 (A5)
unnamed: R4.1, U3.26 (SCL)
unnamed: R5.1, U3.27 (SDA)
unnamed: R8.2, U4.2 (IN)
unnamed: R9.2, U4.3 (INH)
unnamed: R23.1, U4.6 (IS)
unnamed: C25.2, R12.2, U4.5 (SR)
unnamed: R10.2, U5.2 (IN)
unnamed: R11.2, U5.3 (INH)
unnamed: R24.1, U5.6 (IS)
unnamed: C26.2, R22.2, U5.5 (SR)
unnamed: R13.2, U6.2 (IN)
unnamed: R14.2, U6.3 (INH)
unnamed: R19.1, U6.6 (IS)
unnamed: C20.2, R17.2, U6.5 (SR)
unnamed: R15.2, U7.2 (IN)
unnamed: R16.2, U7.3 (INH)
unnamed: R20.1, U7.6 (IS)
unnamed: C21.2, R18.2, U7.5 (SR)
unnamed: R26.1, R27.2, U8.2 (FB)
unnamed: D4.1, L3.1, U8.3 (SW)
unnamed: C31.2, U8.4 (VC)

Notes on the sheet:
Điều khiển Đ/Cơ
Jack kết nối
Mở rộng chân PWM
Khối Nguồn
Khuếch đại loa

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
